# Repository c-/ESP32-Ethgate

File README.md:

# ESP32-Ethgate

This is an ESP32 (ESP32-WROOM-32 module) with LAN8720A PHY project
intended to be an ESP-NOW to (wired) MQTT gateway.

It was designed to be produced in my PCB mill. If your PCB mill can handle
QFN24 footprints and double-sided PCB's then you might be able to duplicate
this. Or you can just order a PCB from pretty much anywhere.
[I had a few made by Oshpark](https://oshpark.com/shared_projects/cBIYloft).

# Design

For simplicity, it uses the GPIO17 PLL clock technique rather than
the GPIO0-based crystal, and includes a second 3.3v regulator to control
the entire ethernet power rail independently. It needs stable USB power,
although at some point I might take a stab at a PoE version.

The CH340C runs off the first regulator along with the ESP32. The HT7233 is
rated for 300mA, which is just marginal for an ESP32, but so far I haven't
noticed any power issues (power consumption for the whole board averages
maybe 250mA). I've thrown in some USB ESD protection, a fuse,
and some reverse protection (I know that's not supposed to be a problem
with USB... things happen, don't ask). ESD protection for the Ethernet
port would be a nice-to-have at some point.

The CH340C supports the usual auto-programming. Note that you *may* 
need to dial back the default upload baud rate.

I've added a small (1.25mm pitch) header with 3V3, GND, and two GPIO's
to allow for things like environmental sensors. Note that temperature
sensors will need to stay a minimum of 10cm off the board to avoid the heat
thrown by this board. I've also broken out the USB interface with a small
header (uUSB connectors can be brittle pieces of junk).

# BOM

Most of the components are from LCSC. There's an interactive BOM page
which should tell you what you need. Passives are 0603 with a few
0805 for the larger capacitors.

# Firmware

The Arduino-ESP32 ETH_LAN8720 sketch should work with the following
configuration:

```
#define LED_BUILTIN 2	// or use a NodeMCU-type of board definition
#define ETH_CLK_MODE    ETH_CLOCK_GPIO17_OUT
#define ETH_POWER_PIN   12
#define ETH_TYPE        ETH_PHY_LAN8720
#define ETH_ADDR        1
#define ETH_MDC_PIN     23
#define ETH_MDIO_PIN    18

ETH.begin(ETH_ADDR, ETH_POWER_PIN, ETH_MDC_PIN, ETH_MDIO_PIN,
	ETH_TYPE, ETH_CLK_MODE)
```

I flash mine with the ESP32 clock set at 80MHz, which seems to be
more stable at 100Mbps connection speeds and draws approximately 25%
less power.

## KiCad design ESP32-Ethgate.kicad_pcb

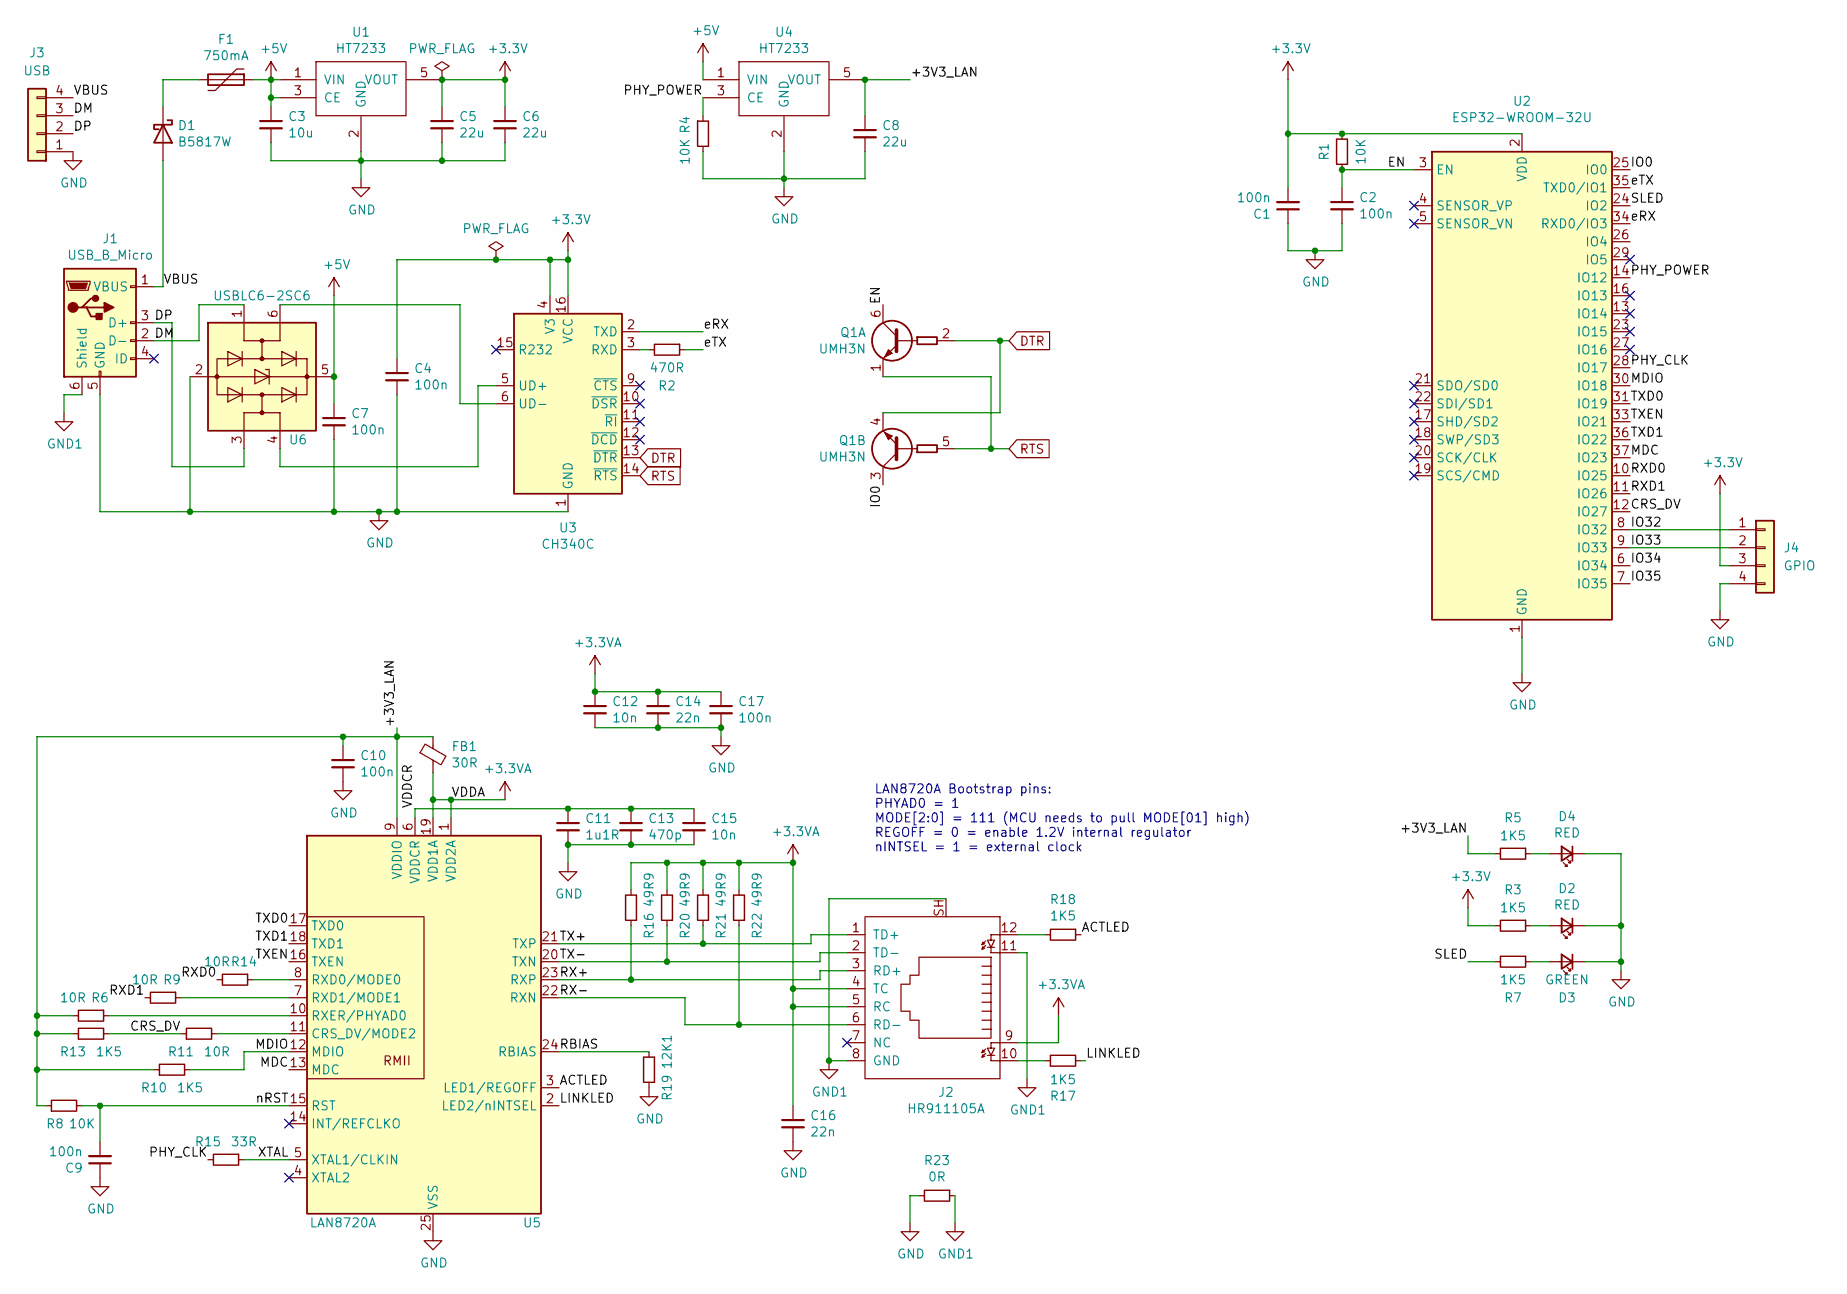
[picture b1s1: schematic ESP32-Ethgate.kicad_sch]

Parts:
C1, C2, C4, C7, C9, C10, C17: 100n; C_0603_1608Metric
C3: 10u; C_0805_2012Metric
C5, C6, C8: 22u; C_0805_2012Metric
C11: 1u1R; C_0603_1608Metric
C12, C15: 10n; C_0603_1608Metric
C13: 470p; C_0603_1608Metric
C14, C16: 22n; C_0603_1608Metric
D1: B5817W; D_SOD-323_HandSoldering
D2, D4: RED; LED_0603_1608Metric_Castellated
D3: GREEN; LED_0603_1608Metric_Castellated
F1: 750mA; Fuse_0805_2012Metric_Pad1.15x1.40mm_HandSolder
FB1: 30R; L_0603_1608Metric
J1: USB_B_Micro; USB_Micro-B_CNC_C10418
J2: HR911105A; RJ45_Hanrun_HR911105A_Oval
J3: USB; Molex_PicoBlade_53047-0410_1x04_P1.25mm_Vertical
J4: GPIO; Molex_PicoBlade_53047-0410_1x04_P1.25mm_Vertical
Q1: UMH3N; SOT-363_SC-70-6_Handsoldering
R1, R4, R8: 10K; R_0603_1608Metric
R2: 470R; R_0603_1608Metric
R3, R5, R7, R10, R13, R17, R18: 1K5; R_0603_1608Metric
R6, R9, R11, R14: 10R; R_0603_1608Metric
R15: 33R; R_0603_1608Metric
R16, R20, R21, R22: 49R9; R_0603_1608Metric
R19: 12K1; R_0603_1608Metric
R23: 0R; R_0603_1608Metric
U1, U4: HT7233; SOT-23-5
U2: ESP32-WROOM-32U; ESP32-WROOM-32U-HandSoldering
U3: CH340C; SOIC-16_3.9x9.9mm_P1.27mm
U5: LAN8720A; QFN-24-1EP_4x4mm_P0.5mm_EP2.6x2.6mm
U6: USBLC6-2SC6; SOT-23-6_Handsoldering

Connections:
+3.3VA: C12.1, C14.1, C16.1, C17.1, FB1.2, J2.4 (TC), J2.5 (RC), J2.9, R16.2, R20.2, R21.2, R22.2, U5.1 (VDD2A), U5.19 (VDD1A)
+3V3: C1.2, C4.1, C5.1, C6.1, J4.3, R1.2, R3.2, U1.5 (VOUT), U2.2 (VDD), U3.4 (V3), U3.16 (VCC)
+5V: C3.1, C7.1, F1.1, U1.1 (VIN), U1.3 (CE), U4.1 (VIN), U6.5 (VBUS)
/+3V3_LAN: C8.1, C10.1, FB1.1, R5.2, R6.2, R8.1, R10.1, R13.1, U4.5 (VOUT), U5.9 (VDDIO)
/ACTLED: R18.1, U5.3 (LED1/REGOFF)
/CRS_DV: R11.1, R13.2, U2.12 (IO27)
/DM: J1.2 (D-), J3.3, U6.1 (I/O1)
/DP: J1.3 (D+), J3.2, U6.3 (I/O2)
/EN: C2.1, Q1.6 (C1), R1.1, U2.3 (EN)
/IO0: Q1.3 (C2), U2.25 (IO0)
/IO32: J4.1, U2.8 (IO32)
/IO33: J4.2, U2.9 (IO33)
/IO34: U2.6 (IO34)
/IO35: U2.7 (IO35)
/LINKLED: R17.2, U5.2 (LED2/nINTSEL)
/MDC: U2.37 (IO23), U5.13 (MDC)
/MDIO: R10.2, U2.30 (IO18), U5.12 (MDIO)
/PHY_CLK: R15.2, U2.28 (IO17)
/PHY_POWER: R4.1, U2.14 (IO12), U4.3 (CE)
/RBIAS: R19.2, U5.24 (RBIAS)
/RX+: J2.3 (RD+), R16.1, U5.23 (RXP)
/RX-: J2.6 (RD-), R22.1, U5.22 (RXN)
/RXD0: R14.2, U2.10 (IO25)
/RXD1: R9.2, U2.11 (IO26)
/SLED: R7.2, U2.24 (IO2)
/TX+: J2.1 (TD+), R21.1, U5.21 (TXP)
/TX-: J2.2 (TD-), R20.1, U5.20 (TXN)
/TXD0: U2.31 (IO19), U5.17 (TXD0)
/TXD1: U2.36 (IO22), U5.18 (TXD1)
/TXEN: U2.33 (IO21), U5.16 (TXEN)
/VBUS: D1.2 (A), J1.1 (VBUS), J3.4
/VDDCR: C11.1, C13.1, C15.1, U5.6 (VDDCR)
/XTAL: R15.1, U5.5 (XTAL1/CLKIN)
/eRX: U2.34 (RXD0/IO3), U3.2 (TXD)
/eTX: R2.1, U2.35 (TXD0/IO1)
/nRST: C9.2, R8.2, U5.15 (RST)
DTR: Q1.2 (B1), Q1.4 (E2), U3.13 (~DTR)
GND: C1.1, C2.2, C3.2, C4.2, C5.2, C6.2, C7.2, C8.2, C9.1, C10.2, C11.2, C12.2, C13.2, C14.2, C15.2, C16.2, C17.2, D2.1 (K), D3.1 (K), D4.1 (K), J1.5 (GND), J3.1, J4.4, R4.2, R19.1, R23.2, U1.2 (GND), U2.1 (GND), U2.15 (GND), U2.38 (GND), U2.39 (GND), U3.1 (GND), U4.2 (GND), U5.25 (VSS), U6.2 (GND)
GND1: J1.6 (Shield), J2.8 (GND), J2.11, J2.SH, R23.1
unnamed: D1.1 (K), F1.2
unnamed: D2.2 (A), R3.1
unnamed: D3.2 (A), R7.1
unnamed: D4.2 (A), R5.1
unnamed: J2.10, R17.1
unnamed: J2.12, R18.2
unnamed: R2.2, U3.3 (RXD)
unnamed: U3.5 (UD+), U6.4 (I/O2)
unnamed: U3.6 (UD-), U6.6 (I/O1)
unnamed: R11.2, U5.11 (CRS_DV/MODE2)
unnamed: R14.1, U5.8 (RXD0/MODE0)
unnamed: R9.1, U5.7 (RXD1/MODE1)
unnamed: R6.1, U5.10 (RXER/PHYAD0)
RTS: Q1.1 (E1), Q1.5 (B2), U3.14 (~RTS)

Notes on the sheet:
LAN8720A Bootstrap pins: PHYAD0 = 1 MODE[2:0] = 111 (MCU needs to pull MODE[01] high) REGOFF = 0 = enable 1.2V internal regulator nINTSEL = 1 = external clock

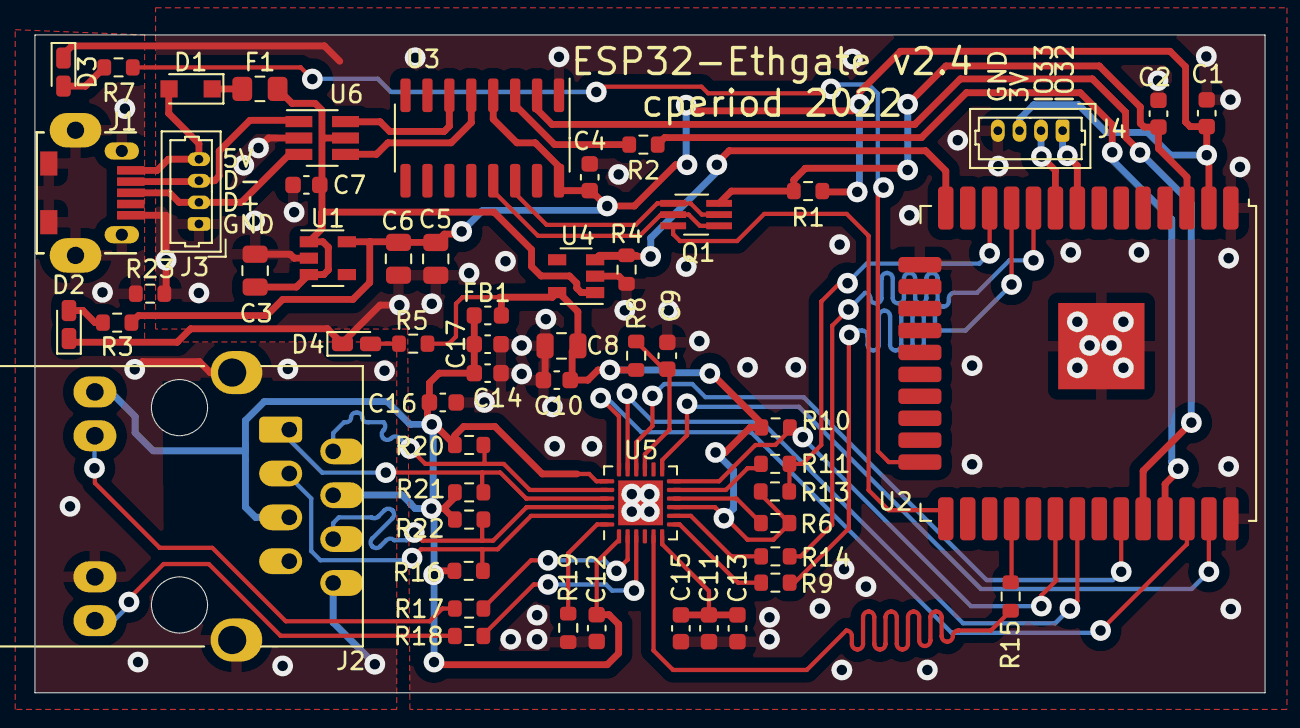
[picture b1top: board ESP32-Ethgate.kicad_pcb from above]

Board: 2 copper layers, 71.2 x 38.1 mm, 56 parts (0 on the bottom side), 51 nets.

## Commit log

2021-03-07 first stab based on W5500. Going to try something else.
2021-03-14 finished layout
2021-04-02 add USB ESD, generate rounded tracks version
2021-05-11 more tweaks
2021-07-10 better, but still not working.
2021-07-12 Working schematic, with proper ethernet connector pinouts
2021-07-12 some layout tweaks to clean things up and make assembly a hair easier
2021-07-12 chop the ground plane up a bit less
2021-07-14 nothing major
2021-07-17 more layout tweaks
2021-07-19 more tuning
2021-07-20 add some documentation
2021-07-21 a note on clock speed
2021-10-03 add a case
2021-10-05 more case tweaks
2021-10-05 update docs
2021-10-05 wrong photo
2021-11-15 PDF schematic
2022-11-01 update Kicad
    make sure REGOFF is properly pulled low, fixing #1
    add some 1.25mm pitch connectors for USB and a couple of GPIO's
    Assorted tweaks to some routing to ensure RMII signals and the clock are
    somewhat length matched.
    Extend the ground exclusion zone to past where the eth magnetics should
    be found.
2022-11-28 update the various extra files
2022-11-28 label the USB connections
2022-11-28 update schematic PDF
2022-11-28 minor doc update
2023-01-11 Create LICENSE.md
    Fixes #2.
2023-07-22 properly fix the nINTSEL for #1 (and document the bootstrap settings in the schematic so I remember next time).
    this implicitly updates to Kicad 7.
2023-07-22 update pdf
2023-07-22 update rev number
2023-07-22 fix some silk designators
2024-03-28 rewriting the firmware after I stupidly deleted that last version
2024-04-18 nothing big
2024-04-18 small tweaks
2024-04-18 swapped the GND/3V labels
2024-04-18 first stab at recreating the firmware
2024-04-18 a few small fixes
2024-04-18 add a photo of the v2.4 board, and shrink the images down to something reasonable
2024-04-18 update OSH Park link
2024-04-18 minor doc updates
2024-04-19 just a hair longer/wider to make room
2024-04-19 get the OTA uploading working again
